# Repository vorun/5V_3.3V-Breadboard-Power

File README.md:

# 5V_3.3V-Breadboard-Power

Simple one layer board for powering breadboards with 12V DC adaptor that can be printed at home.

-3.3V output is mostly for powering microcontrollers and IC's. 5V can output up to 1 Amp's of current with proper heatsink.

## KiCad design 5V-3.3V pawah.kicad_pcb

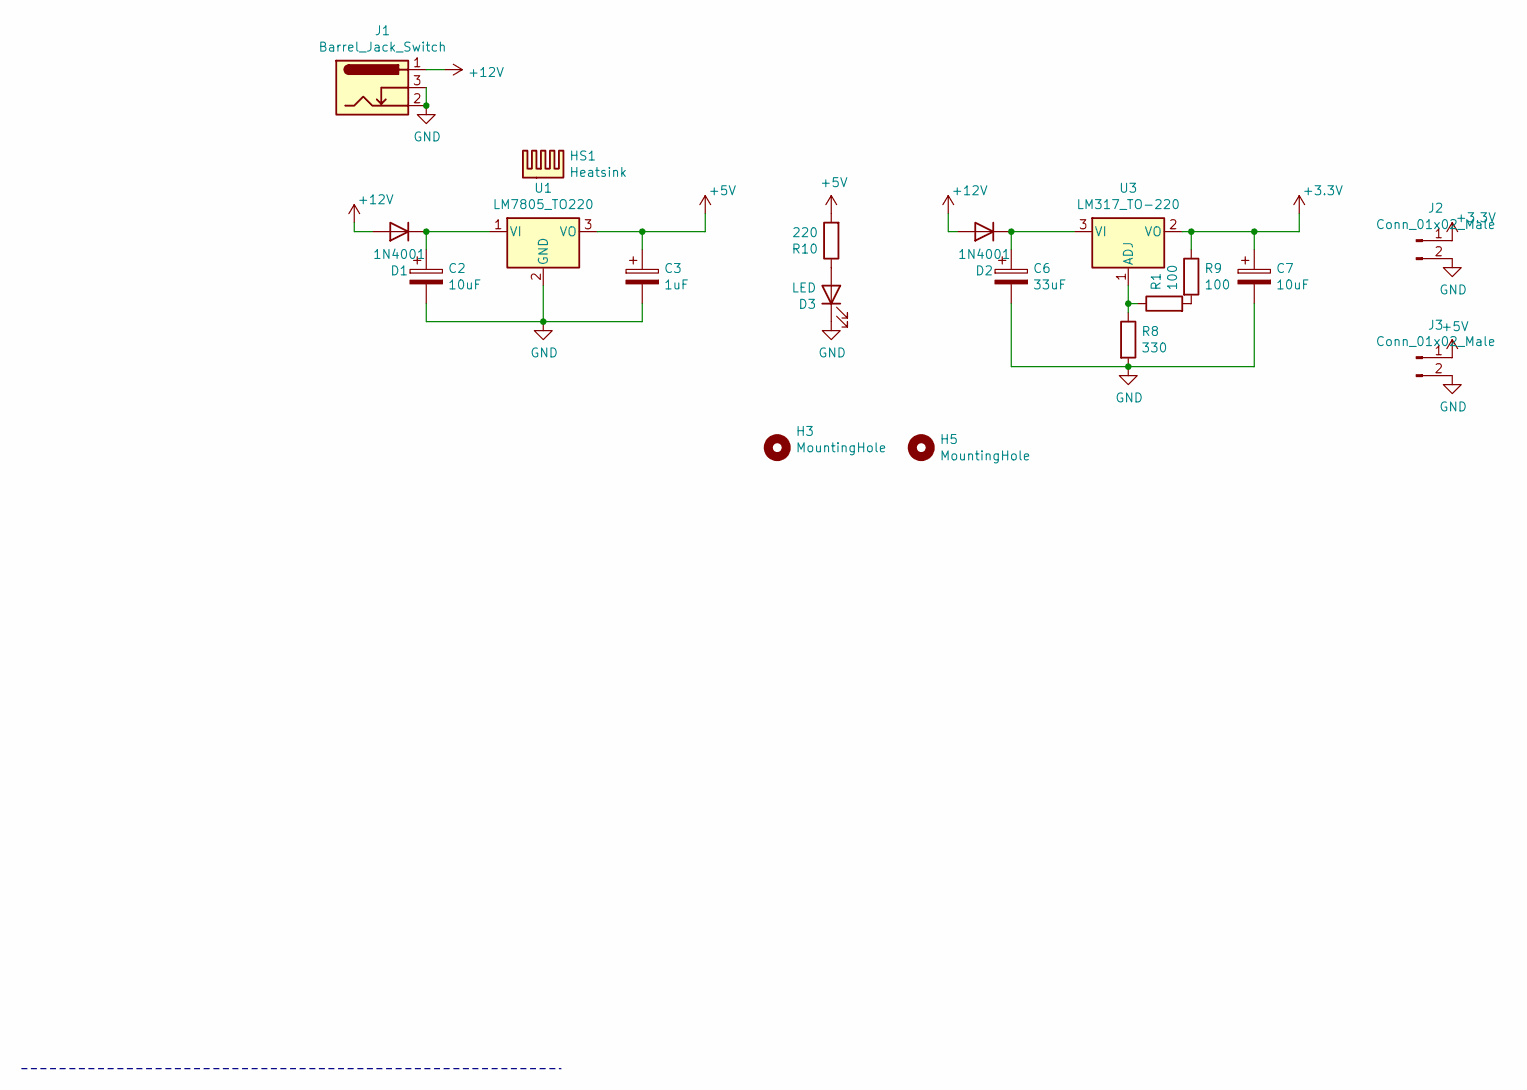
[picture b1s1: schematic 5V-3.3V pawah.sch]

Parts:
C2, C7: 10uF; CP_EIA-6032-28_Kemet-C_Pad2.25x2.35mm_HandSolder
C3: 1uF; CP_EIA-3528-21_Kemet-B_Pad1.50x2.35mm_HandSolder
C6: 33uF; CP_Elec_6.3x5.2
D1, D2: 1N4001; D_DO-41_SOD81_P7.62mm_Horizontal
D3: LED; LED_1210_3225Metric_Pad1.42x2.65mm_HandSolder
H3, H5: MountingHole; MountingHole_3.2mm_M3_Pad_Via
HS1: Heatsink; Heatsink_TO220
J1: Barrel_Jack_Switch; BarrelJack_Horizontal
J2, J3: Conn_01x02_Male; PinHeader_1x02_P2.54mm_Vertical
R1, R9: 100; R_1210_3225Metric_Pad1.30x2.65mm_HandSolder
R8: 330; R_1210_3225Metric_Pad1.30x2.65mm_HandSolder
R10: 220; R_Axial_DIN0207_L6.3mm_D2.5mm_P10.16mm_Horizontal
U1: LM7805_TO220; TO-220-3_Vertical
U3: LM317_TO-220; SOT-223-3_TabPin2

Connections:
+3V3: C7.1, J2.1, R9.1, U3.2 (VO)
+5V: C3.1, J3.1, R10.2, U1.3 (VO)
+12V: D1.2 (A), D2.2 (A), J1.1
GND: C2.2, C3.2, C6.2, C7.2, D3.1 (K), J1.2, J1.3, J2.2, J3.2, R8.2, U1.2 (GND)
unnamed: C2.1, D1.1 (K), U1.1 (VI)
unnamed: C6.1, D2.1 (K), U3.3 (VI)
unnamed: D3.2 (A), R10.1
unnamed: R1.1, R8.1, U3.1 (ADJ)
unnamed: R1.2, R9.2

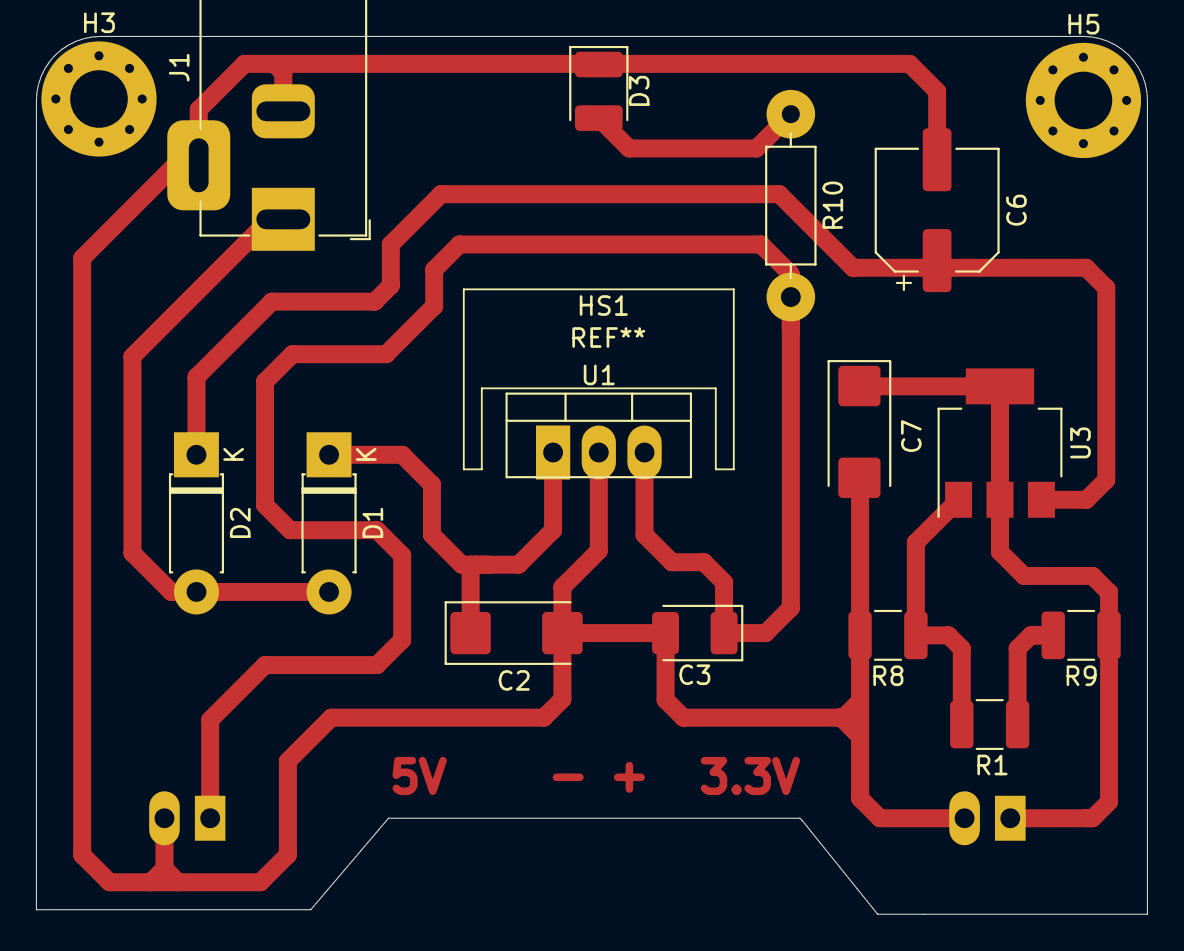
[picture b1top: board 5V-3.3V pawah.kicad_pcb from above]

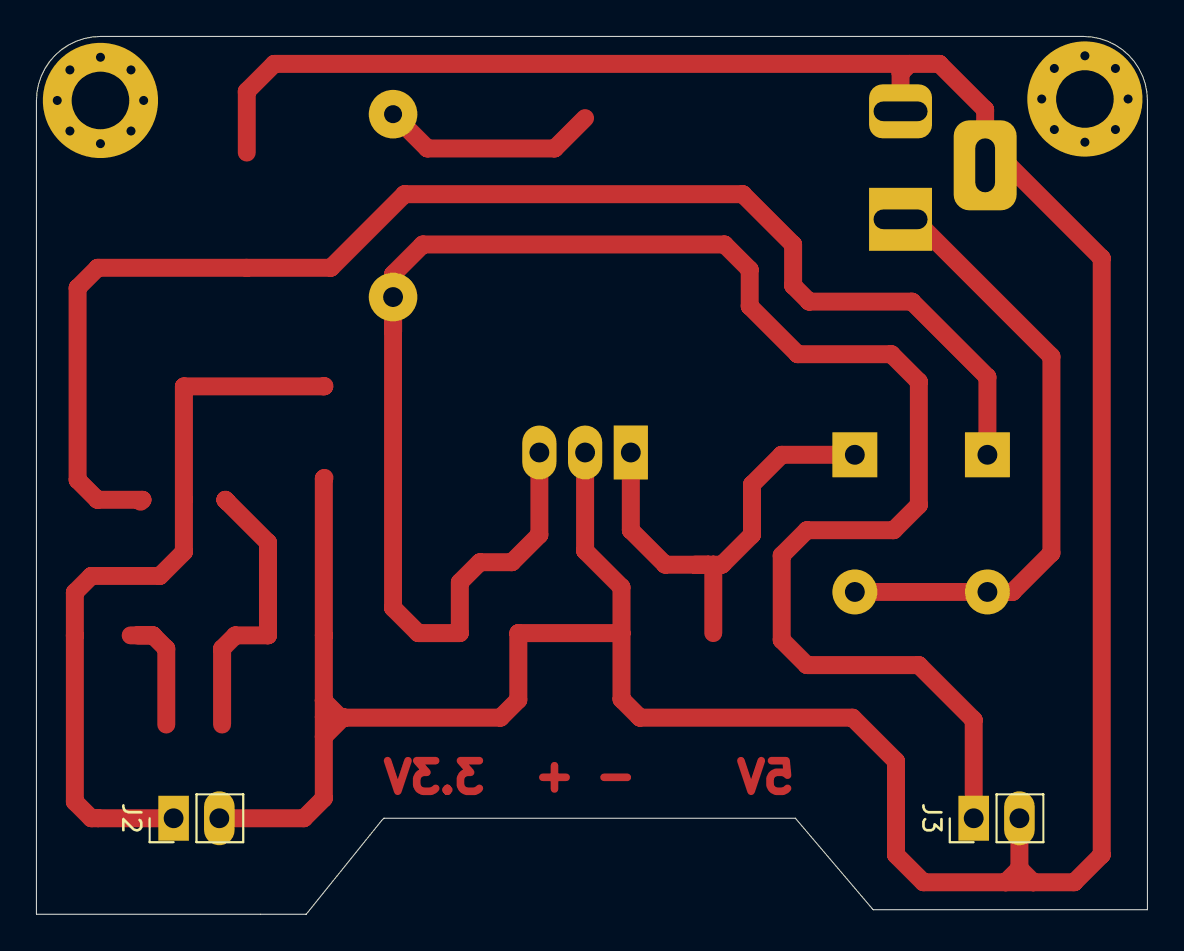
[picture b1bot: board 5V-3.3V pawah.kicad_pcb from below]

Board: 2 copper layers, 61.7 x 48.8 mm, 19 parts (2 on the bottom side), 9 nets.

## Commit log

2022-06-18 Update PCB
2022-06-18 PCB Updated
2022-06-18 ^D added
2022-06-29 3D Updated
